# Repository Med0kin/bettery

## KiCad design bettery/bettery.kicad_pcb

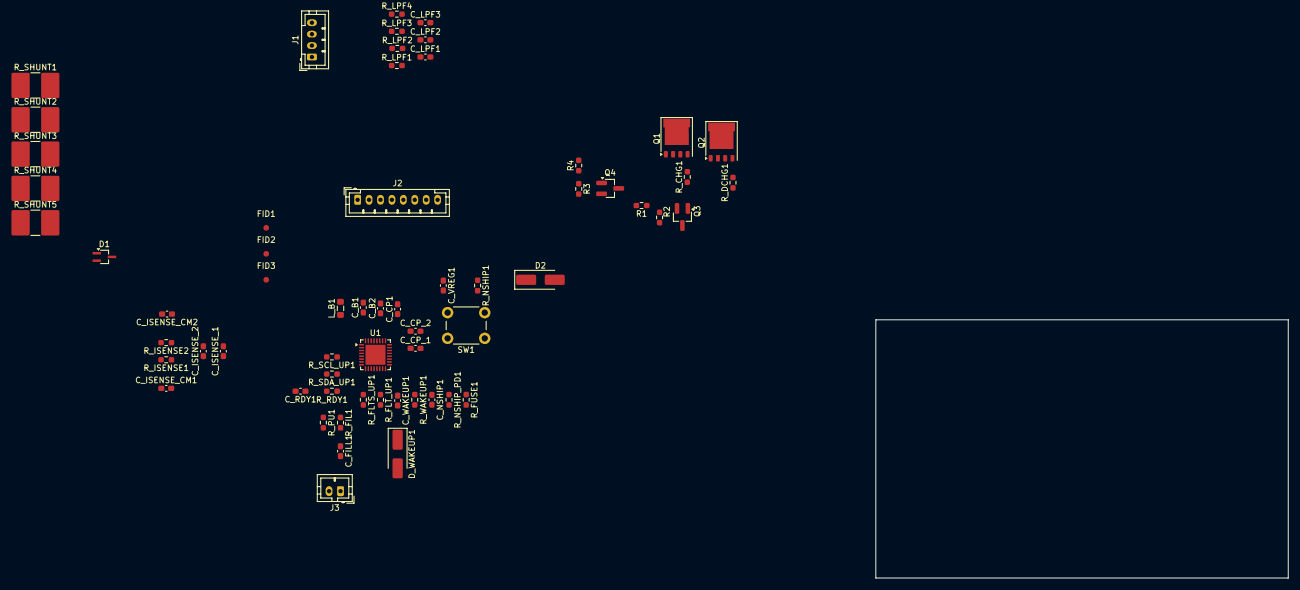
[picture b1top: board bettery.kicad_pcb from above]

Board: 2 copper layers, 72.2 x 45.2 mm, 61 parts (0 on the bottom side), 42 nets, no tracks yet.

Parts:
C_B1: 10u; C_0603_1608Metric_Pad1.08x0.95mm_HandSolder
C_B2: 220n; C_0603_1608Metric_Pad1.08x0.95mm_HandSolder
C_CP1: 68n; C_0603_1608Metric_Pad1.08x0.95mm_HandSolder
C_CP_1, C_CP_2: 6.8n; C_0603_1608Metric_Pad1.08x0.95mm_HandSolder
C_FILL1: 10n; C_0603_1608Metric_Pad1.08x0.95mm_HandSolder
C_ISENSE_1: 4.7u; C_0603_1608Metric_Pad1.08x0.95mm_HandSolder
C_ISENSE_2: 22n; C_0603_1608Metric_Pad1.08x0.95mm_HandSolder
C_ISENSE_CM1, C_ISENSE_CM2: 4.7u; C_0603_1608Metric_Pad1.08x0.95mm_HandSolder
C_LPF1, C_LPF2, C_LPF3: 470n; C_0603_1608Metric_Pad1.08x0.95mm_HandSolder
C_NSHIP1: 100n; C_0603_1608Metric_Pad1.08x0.95mm_HandSolder
C_RDY1: 100p; C_0603_1608Metric_Pad1.08x0.95mm_HandSolder
C_VREG1: 4.7u; C_0603_1608Metric_Pad1.08x0.95mm_HandSolder
C_WAKEUP1: 100n; C_0603_1608Metric_Pad1.08x0.95mm_HandSolder
D1: BAT54SWFILMY; SOT-323_SC-70_Handsoldering
D2: SS54; D_SMA_Handsoldering
D_WAKEUP1: SS54; D_SMA_Handsoldering
FID1, FID2, FID3: Fiducial; Fiducial_1mm_Mask3mm
J1: JST_PH_B4B-PH-K_1x04_P2.00mm_Vertical
J2: JST_PH_B8B-PH-K_1x08_P2.00mm_Vertical
J3: JST_PH_B2B-PH-K_1x02_P2.00mm_Vertical
L_B1: 1u; L_0805_2012Metric_Pad1.05x1.20mm_HandSolder
Q1, Q2: WMB014N06LG4; WMB014N06LG4-PDFN5060-8L
Q3: SL2319A; SOT-23_Handsoldering
Q4: MMBT3904; SOT-23_Handsoldering
R1: 1M; R_0603_1608Metric_Pad0.98x0.95mm_HandSolder
R2: 330k; R_0603_1608Metric_Pad0.98x0.95mm_HandSolder
R3: 47k; R_0603_1608Metric_Pad0.98x0.95mm_HandSolder
R4: 10k; R_0603_1608Metric_Pad0.98x0.95mm_HandSolder
R_CHG1: 2M; R_0603_1608Metric_Pad0.98x0.95mm_HandSolder
R_DCHG1: 2M; R_0603_1608Metric_Pad0.98x0.95mm_HandSolder
R_FIL1: 10k; R_0603_1608Metric_Pad0.98x0.95mm_HandSolder
R_FLTS_UP1: 4.7k; R_0603_1608Metric_Pad0.98x0.95mm_HandSolder
R_FLT_UP1: 4.7k; R_0603_1608Metric_Pad0.98x0.95mm_HandSolder
R_FUSE1: 10k; R_0603_1608Metric_Pad0.98x0.95mm_HandSolder
R_ISENSE1, R_ISENSE2: 22; R_0603_1608Metric_Pad0.98x0.95mm_HandSolder
R_LPF1, R_LPF2, R_LPF3, R_LPF4: 39; R_0603_1608Metric_Pad0.98x0.95mm_HandSolder
R_NSHIP1: 10k; R_0603_1608Metric_Pad0.98x0.95mm_HandSolder
R_NSHIP_PD1: 100k; R_0603_1608Metric_Pad0.98x0.95mm_HandSolder
R_PU1: 33k; R_0603_1608Metric_Pad0.98x0.95mm_HandSolder
R_RDY1: 100; R_0603_1608Metric_Pad0.98x0.95mm_HandSolder
R_SCL_UP1: 4.7k; R_0603_1608Metric_Pad0.98x0.95mm_HandSolder
R_SDA_UP1: 4.7k; R_0603_1608Metric_Pad0.98x0.95mm_HandSolder
R_SHUNT1, R_SHUNT2, R_SHUNT3, R_SHUNT4, R_SHUNT5: 10m; R_2816_7142Metric_Pad3.20x4.45mm_HandSolder
R_WAKEUP1: 1k; R_0603_1608Metric_Pad0.98x0.95mm_HandSolder
SW1: SW_Push; SW_PUSH_6mm
U1: L9961; UFQFPN-32-1EP_5x5mm_P0.5mm_EP3.5x3.5mm

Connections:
+BATT: D1.1 (A), Q1.1 (S), R_CHG1.1, U1.19 (VSC)
+PACK: D2.1 (K), Q2.1 (S), R_DCHG1.1, U1.18 (VSD)
-BATT: C_B1.2, C_B2.2, C_FILL1.2, C_ISENSE_CM1.1, C_ISENSE_CM2.2, C_LPF1.2, C_NSHIP1.2, C_RDY1.2, C_VREG1.2, C_WAKEUP1.2, J2.8, Q4.2 (E), R3.2, R_FUSE1.2, R_ISENSE1.2, R_LPF1.2, R_NSHIP_PD1.1, R_SHUNT1.1, R_SHUNT2.1, R_SHUNT3.1, R_SHUNT4.1, R_SHUNT5.1, U1.1 (C0), U1.4 (GND), U1.13 (GND), U1.27 (GND), U1.31 (C2), U1.32 (C1)
-PACK: D2.2 (A), R_ISENSE2.2, R_SHUNT1.2, R_SHUNT2.2, R_SHUNT3.2, R_SHUNT4.2, R_SHUNT5.2
/C3: C_LPF1.1, C_LPF2.2, R_LPF2.2, U1.30 (C3)
/C4: C_LPF2.1, C_LPF3.2, R_LPF3.2, U1.29 (C4)
/C5: C_LPF3.1, R_LPF4.2, U1.28 (C5)
/CHG: Q3.3 (S), R2.2, U1.20 (CHG)
/DCHG: Q2.2 (G), R_DCHG1.2, U1.17 (DCHG)
/FAULTN: J2.3, R_FLT_UP1.1, U1.12 (FAULTN)
/FAULTN_SAFE: J2.4, R_FLTS_UP1.1, U1.11 (FAULTN_SAFE)
/FS: J2.1, R4.2
/GPIO3: D_WAKEUP1.2 (A), J2.2
/ISENSEM: C_ISENSE_1.1, C_ISENSE_2.1, C_ISENSE_CM1.2, R_ISENSE1.1, U1.3 (ISENSEM)
/ISENSEP: C_ISENSE_1.2, C_ISENSE_2.2, C_ISENSE_CM2.1, R_ISENSE2.1, U1.2 (ISENSEP)
/NSHIP: C_NSHIP1.1, D_WAKEUP1.1 (K), R_NSHIP_PD1.2, R_WAKEUP1.1, SW1.1, U1.15 (NSHIP)
/NTC: C_FILL1.1, R_FIL1.1, U1.9 (NTC)
/OD: J3.1, U1.10 (OD)
/RDY: J2.5, R_RDY1.2, U1.7 (RDY)
/SCL: J2.7, R_SCL_UP1.1, U1.5 (SCL)
/SDA: J2.6, R_SDA_UP1.1, U1.6 (SDA)
/VB: C_B1.1, C_B2.1, C_CP1.2, L_B1.2, Q1.3 (D), Q2.3 (D), R_NSHIP1.1, U1.26 (VB)
/VREG: C_VREG1.1, R_FLTS_UP1.2, R_FLT_UP1.2, R_PU1.1, R_SCL_UP1.2, R_SDA_UP1.2, U1.8 (VREG)
/WAKEUP: C_WAKEUP1.1, R_WAKEUP1.2, U1.14 (WAKEUP)
unnamed: C_RDY1.1, R_RDY1.1
unnamed: D1.3 (K), L_B1.1
unnamed: J1.1, R_LPF4.1
unnamed: J1.2, R_LPF3.1
unnamed: J1.3, R_LPF2.1
unnamed: J1.4, R_LPF1.1
unnamed: J3.2, R_FIL1.2, R_PU1.2
unnamed: Q1.2 (G), Q3.1 (D), R_CHG1.2
unnamed: Q3.2 (G), R1.1, R2.1
unnamed: Q4.1 (B), R3.1, R4.1
unnamed: Q4.3 (C), R1.2
unnamed: R_NSHIP1.2, SW1.2
unnamed: R_FUSE1.1, U1.16 (FUSE)
unnamed: C_CP_1.2, U1.21 (VCP1M)
unnamed: C_CP_1.1, U1.22 (VCP1P)
unnamed: C_CP_2.2, U1.23 (VCP2M)
unnamed: C_CP_2.1, U1.24 (VCP2P)
unnamed: C_CP1.1, U1.25 (VCP)

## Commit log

2026-01-01 init
